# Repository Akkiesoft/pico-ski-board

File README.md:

# Pico Ski Board

Pico Ski Board is the smallest breakout board for connecting a female pin header cable to the Raspberry Pi Pico without turning the Raspberry Pi Pico upside down.

To use, solder a 1x20 pin socket on the inside and a 1x20 pin header on the outside, and insert Raspberry Pi Pico into the pin socket.

## images

## How to order boards using garber data

* zip garber-rev1 directory
* Upload zip to [JLCPCB](https://jlcpcb.com/) and order.
    * NOTE: With this data, you cannot order for $2. To get it down to $2, you would have to remove one of the ski boards and order it as both left and right.

## To make it more of a ski board

If the pin sockets and pin headers could be surface mounted, it would make it more like a ski board. :)

## License

MIT License

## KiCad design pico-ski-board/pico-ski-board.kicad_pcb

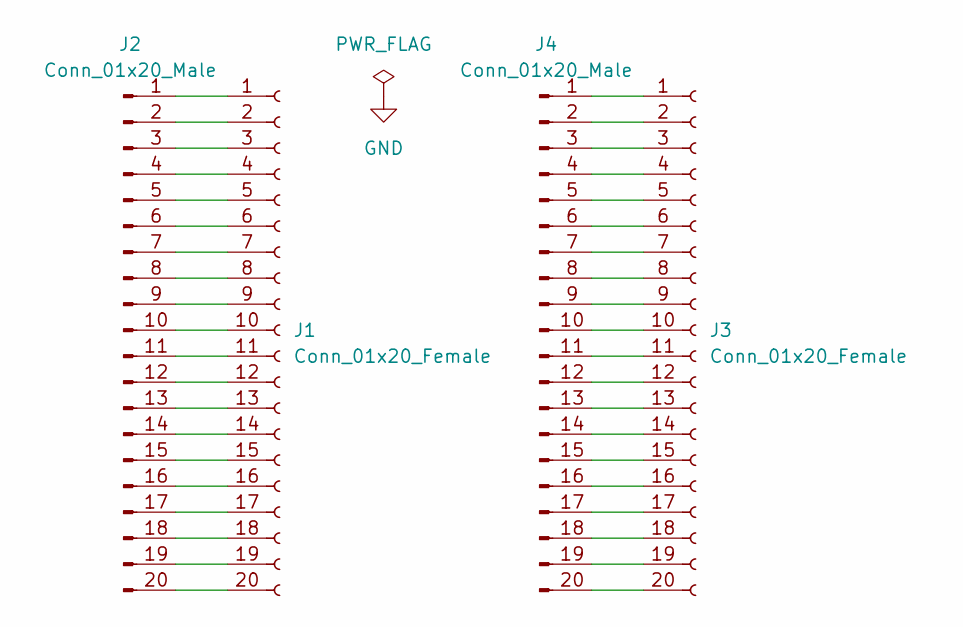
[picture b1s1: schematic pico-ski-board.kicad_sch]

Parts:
J1, J3: Conn_01x20_Female; PinSocket_1x20_P2.54mm_Vertical
J2, J4: Conn_01x20_Male; PinHeader_1x20_P2.54mm_Vertical

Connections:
unnamed: J1.1, J2.1
unnamed: J1.2, J2.2
unnamed: J1.3, J2.3
unnamed: J1.4, J2.4
unnamed: J1.5, J2.5
unnamed: J1.6, J2.6
unnamed: J1.7, J2.7
unnamed: J1.8, J2.8
unnamed: J1.9, J2.9
unnamed: J1.10, J2.10
unnamed: J1.11, J2.11
unnamed: J1.12, J2.12
unnamed: J1.13, J2.13
unnamed: J1.14, J2.14
unnamed: J1.15, J2.15
unnamed: J1.16, J2.16
unnamed: J1.17, J2.17
unnamed: J1.18, J2.18
unnamed: J1.19, J2.19
unnamed: J1.20, J2.20
unnamed: J3.1, J4.1
unnamed: J3.2, J4.2
unnamed: J3.3, J4.3
unnamed: J3.4, J4.4
unnamed: J3.5, J4.5
unnamed: J3.6, J4.6
unnamed: J3.7, J4.7
unnamed: J3.8, J4.8
unnamed: J3.9, J4.9
unnamed: J3.10, J4.10
unnamed: J3.11, J4.11
unnamed: J3.12, J4.12
unnamed: J3.13, J4.13
unnamed: J3.14, J4.14
unnamed: J3.15, J4.15
unnamed: J3.16, J4.16
unnamed: J3.17, J4.17
unnamed: J3.18, J4.18
unnamed: J3.19, J4.19
unnamed: J3.20, J4.20

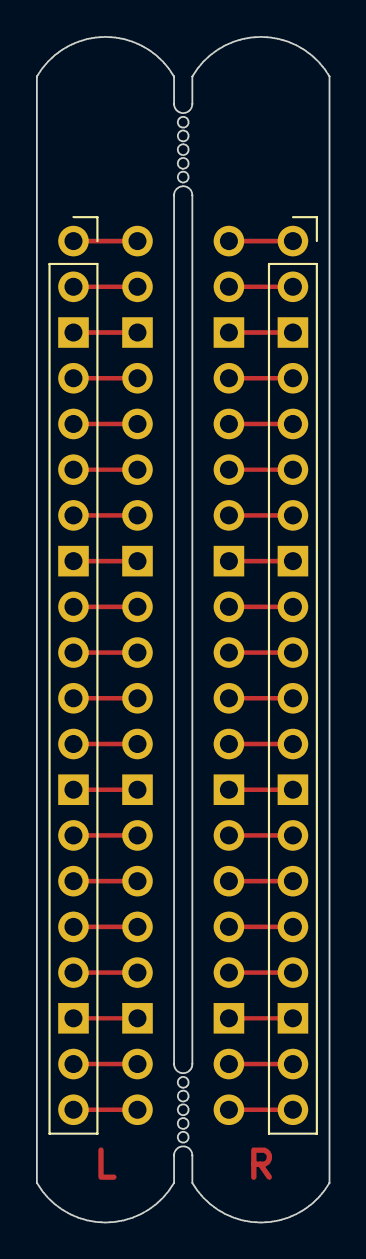
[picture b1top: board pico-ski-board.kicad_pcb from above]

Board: 2 copper layers, 16.3 x 65.9 mm, 4 parts (0 on the bottom side), 40 nets.

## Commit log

2023-05-20 ✌(’ω’)✌
2023-05-23 add photos
